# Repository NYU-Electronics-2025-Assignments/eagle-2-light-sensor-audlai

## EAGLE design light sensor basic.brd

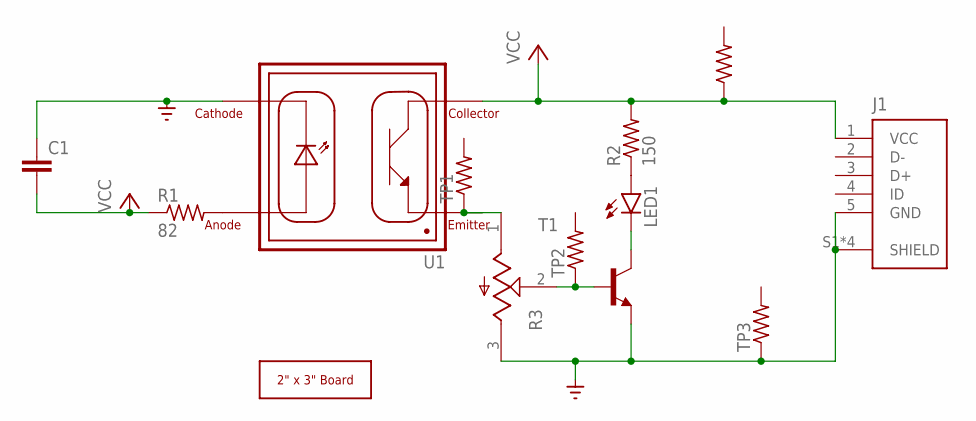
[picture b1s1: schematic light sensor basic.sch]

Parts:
C1: 0.1 uF; C1206
J1: UJ2-MIBH-G-SMT-TR; CUI_UJ2-MIBH-G-SMT-TR
LED1: LEDSML0805; SML0805
R1: 82; R0805
R2: 150; R0805
R3: TC33X-2-203E; TRIM_TC33X-2-203E
T1: -NPN-SOT23-EBC; SOT23-EBC
TP1, TP2, TP3, TP4: R-US_R1206; R1206
U1: VCNT2020; XDCR_VCNT2020
U$1: 2X3_BOARD; 2X3_BOARD_V1

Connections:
GND: C1.1, J1.5 (GND), J1.S1 (SHIELD), J1.S2 (SHIELD), J1.S3 (SHIELD), J1.S4 (SHIELD), R3.3 (CW), T1.E, TP3.1, U1.4 (CATHODE)
unnamed: R1.2, U1.3 (ANODE)
unnamed: R3.1 (CCW), TP1.1, U1.1 (EMITTER)
unnamed: R3.2 (W), T1.B, TP2.1
unnamed: LED1.C, T1.C
unnamed: LED1.A, R2.1
VCC: C1.2, J1.1 (VCC), R1.1, R2.2, TP4.1, U1.2 (COLLECTOR)

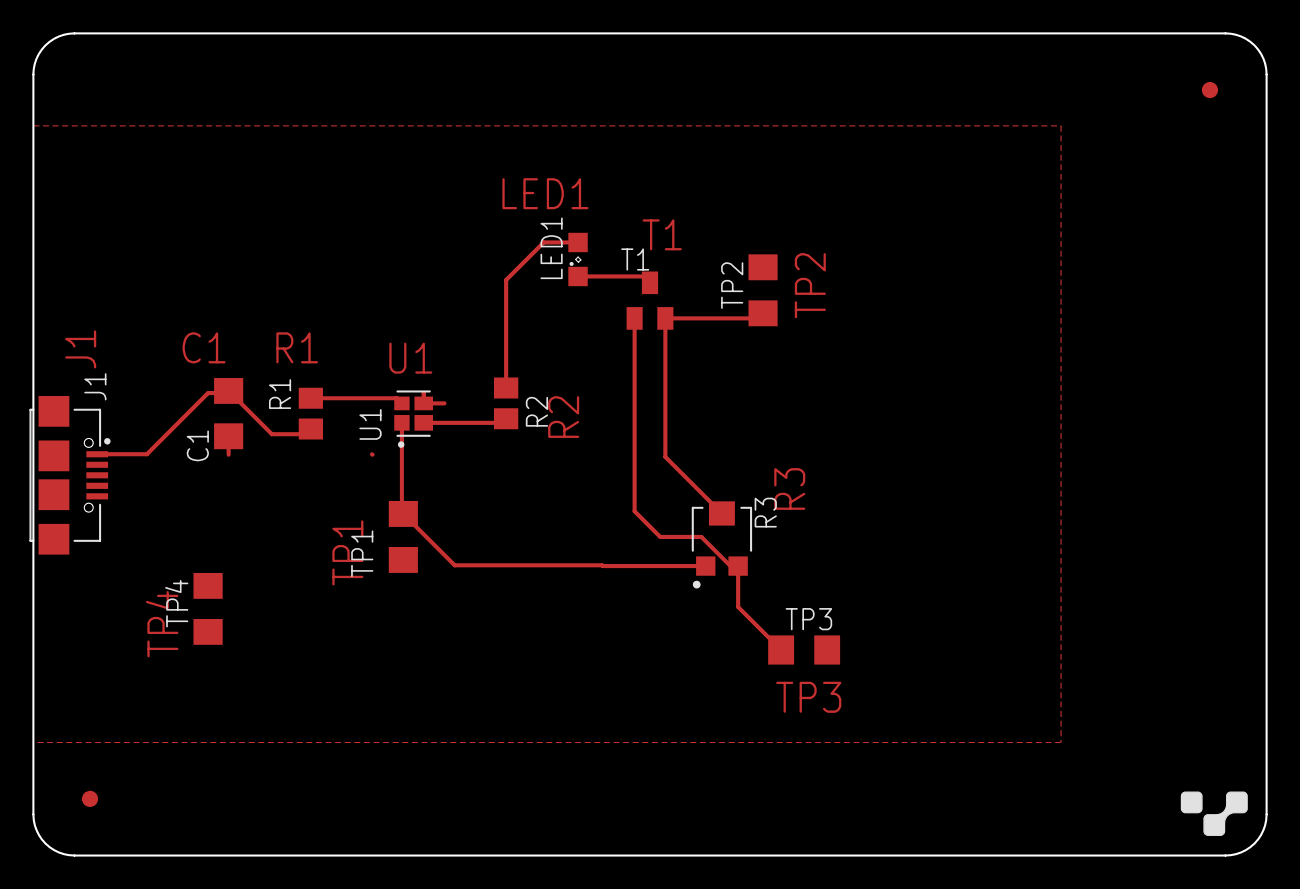
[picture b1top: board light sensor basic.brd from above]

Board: 2 copper layers, 76.2 x 50.8 mm, 13 parts (0 on the bottom side), 7 nets.

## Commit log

2025-03-31 Update board
